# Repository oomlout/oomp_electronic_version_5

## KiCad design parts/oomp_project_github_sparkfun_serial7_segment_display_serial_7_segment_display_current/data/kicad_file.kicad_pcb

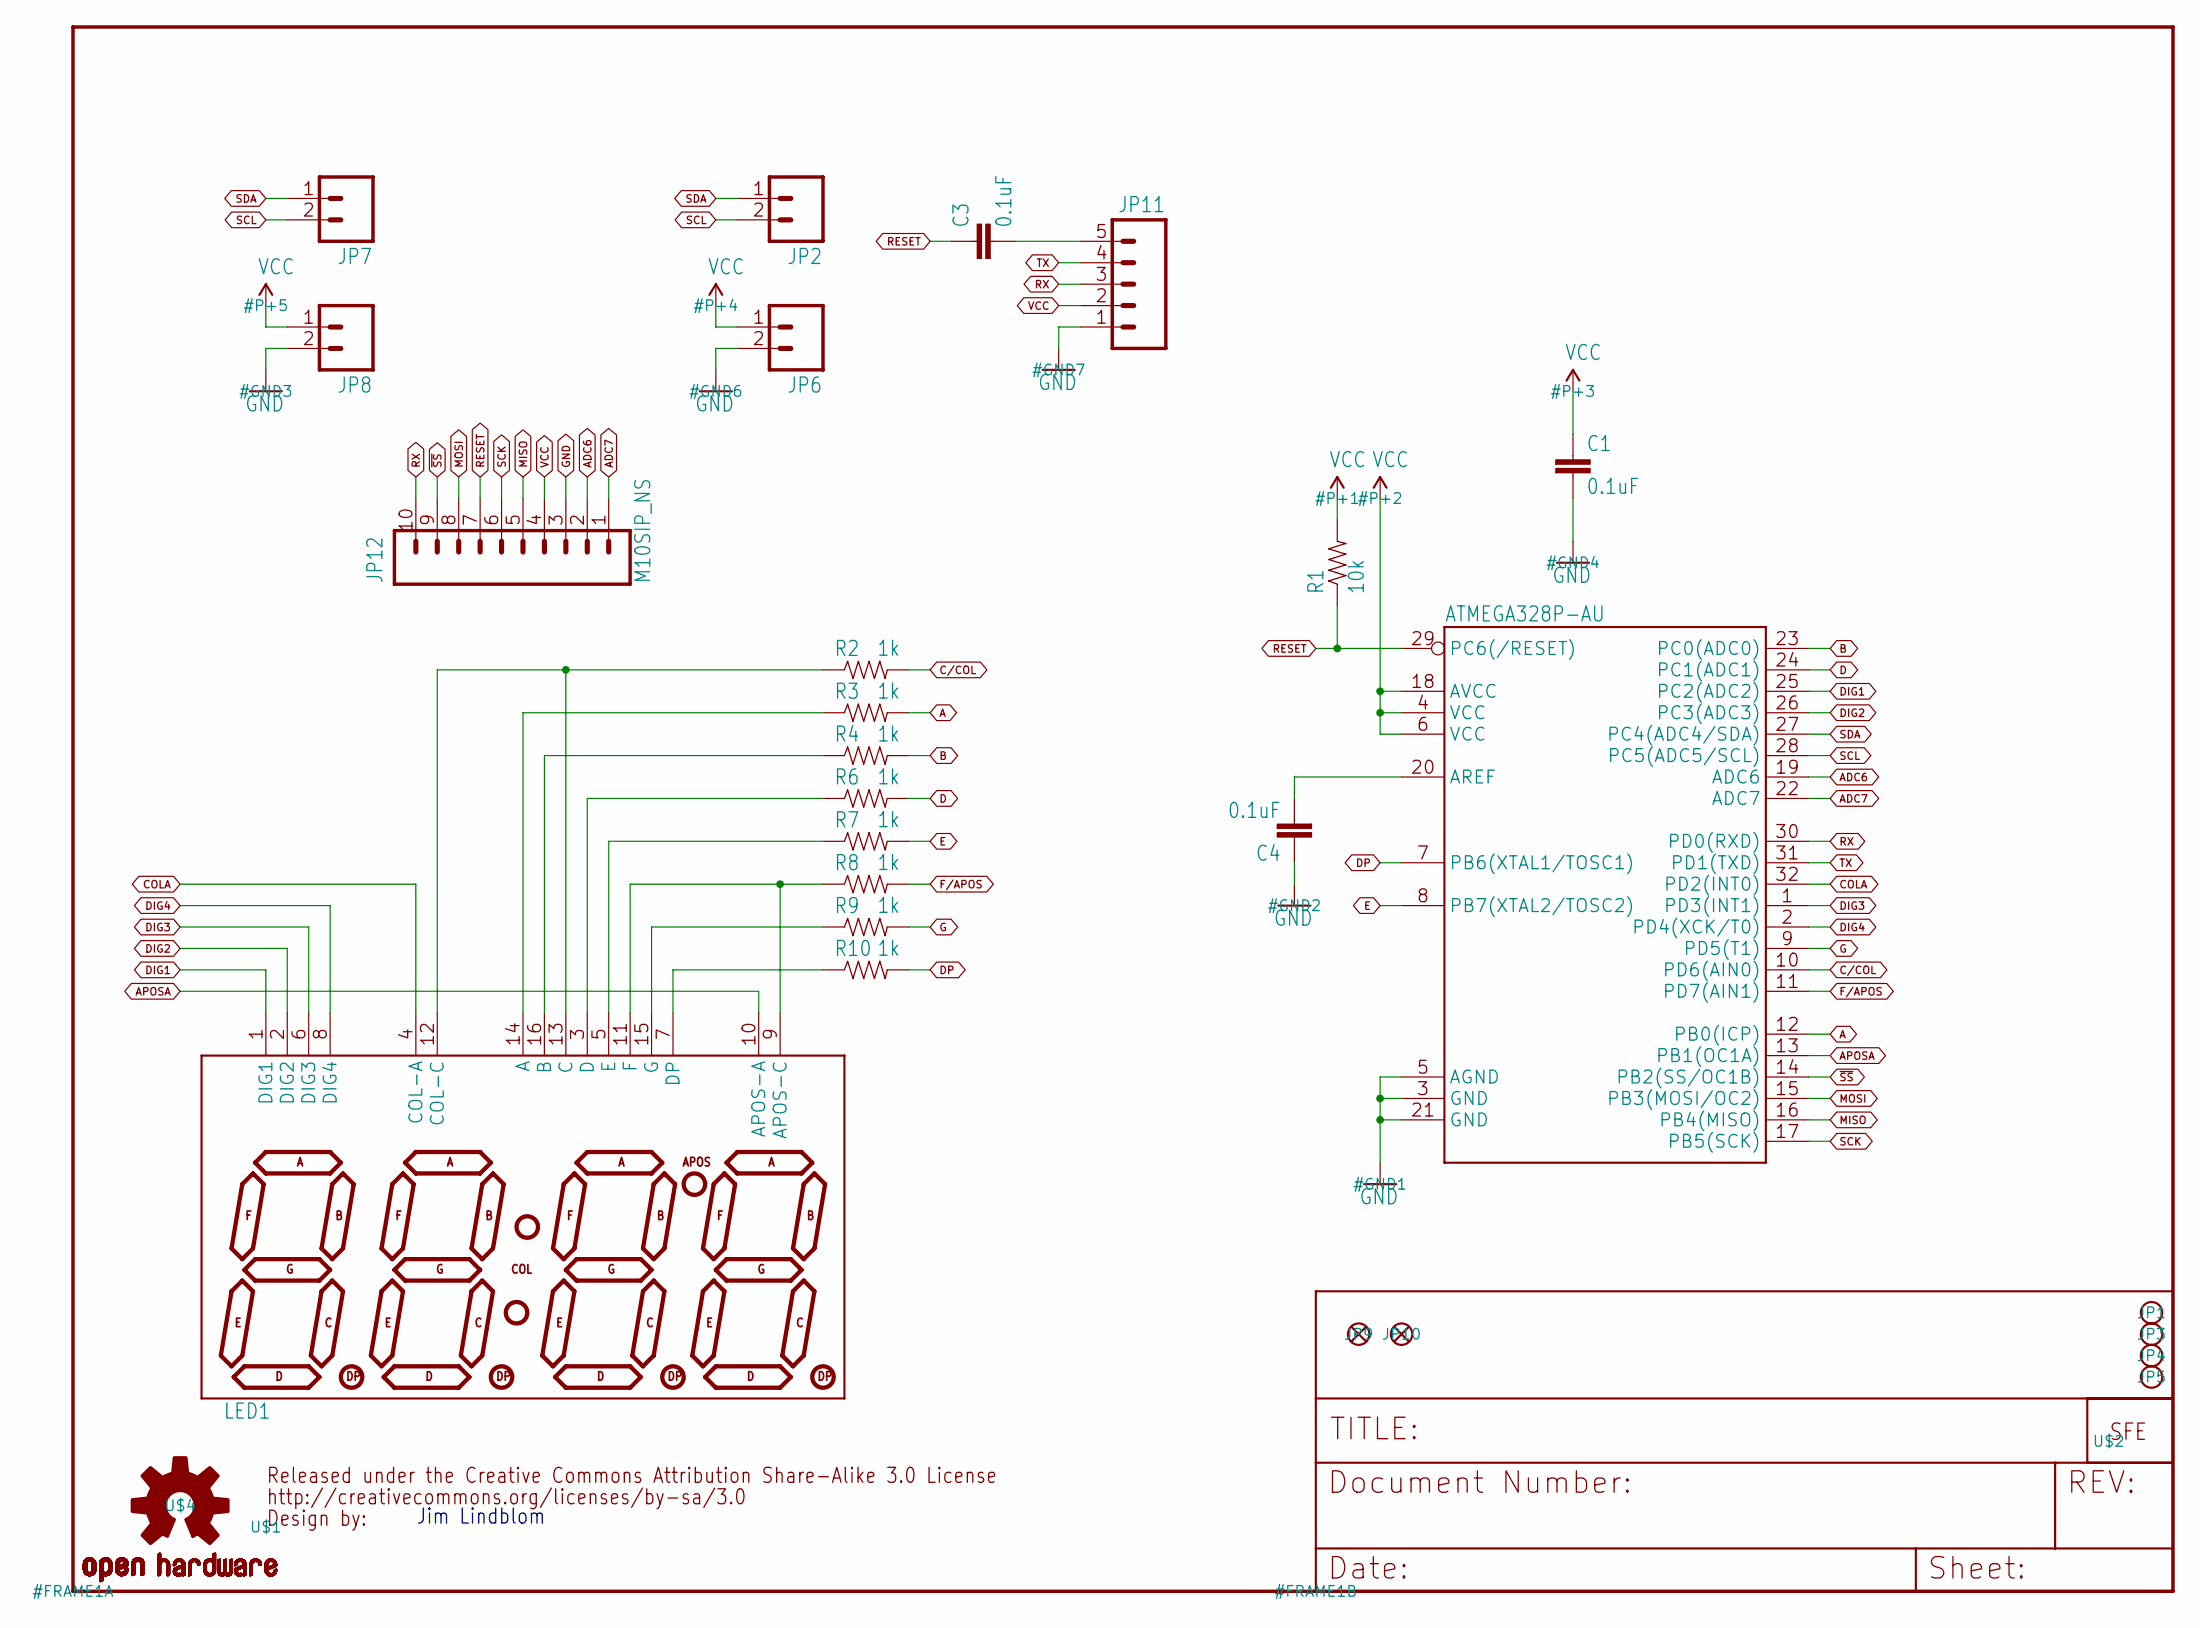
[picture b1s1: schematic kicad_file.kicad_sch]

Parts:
ATMEGA328P-AU0: ATMEGA328P-AU; TQFP32-08
C1, C3, C4: 0.1uF; 0402-CAP
JP1, JP3, JP4, JP5: STAND-OFF
JP2, JP6, JP7, JP8: M021X02_NO_SILK; 1X02_NO_SILK
JP9, JP10: FIDUCIALUFIDUCIAL; MICRO-FIDUCIAL
JP11: M05PTH-NS; 1X05_NO_SILK
JP12: M10SIP_NS; 1X10_NO_SILK
LED1: 7-SEGMENT-4DIGIT-YOUNGSUN
R1: 10k; 0402-RES
R2, R3, R4, R6, R7, R8, R9, R10: 1k; 0402-RES
U$1: CREATIVE_COMMONS
U$2: LOGO-SFESK; SFE-LOGO-FLAME
U$4: OSHW-LOGOS; OSHW-LOGO-S

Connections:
A: ATMEGA328P-AU0.12 (PB0(ICP)), R3.2
ADC6: ATMEGA328P-AU0.19 (ADC6), JP12.2
ADC7: ATMEGA328P-AU0.22 (ADC7), JP12.1
APOSA: ATMEGA328P-AU0.13 (PB1(OC1A)), LED1.10 (APOS-A)
B: ATMEGA328P-AU0.23 (PC0(ADC0)), R4.2
C/COL: ATMEGA328P-AU0.10 (PD6(AIN0)), R2.2
COLA: ATMEGA328P-AU0.32 (PD2(INT0)), LED1.4 (COL-A)
D: ATMEGA328P-AU0.24 (PC1(ADC1)), R6.2
DIG1: ATMEGA328P-AU0.25 (PC2(ADC2)), LED1.1 (DIG1)
DIG2: ATMEGA328P-AU0.26 (PC3(ADC3)), LED1.2 (DIG2)
DIG3: ATMEGA328P-AU0.1 (PD3(INT1)), LED1.6 (DIG3)
DIG4: ATMEGA328P-AU0.2 (PD4(XCK/T0)), LED1.8 (DIG4)
DP: ATMEGA328P-AU0.7 (PB6(XTAL1/TOSC1)), R10.2
E: ATMEGA328P-AU0.8 (PB7(XTAL2/TOSC2)), R7.2
F/APOS: ATMEGA328P-AU0.11 (PD7(AIN1)), R8.2
G: ATMEGA328P-AU0.9 (PD5(T1)), R9.2
GND: ATMEGA328P-AU0.3 (GND), ATMEGA328P-AU0.5 (AGND), ATMEGA328P-AU0.21 (GND), C1.2, C4.1, JP6.2, JP8.2, JP11.1, JP12.3
MISO: ATMEGA328P-AU0.16 (PB4(MISO)), JP12.5
MOSI: ATMEGA328P-AU0.15 (PB3(MOSI/OC2)), JP12.8
unnamed: ATMEGA328P-AU0.20 (AREF), C4.2
unnamed: LED1.7 (DP), R10.1
unnamed: LED1.15 (G), R9.1
unnamed: LED1.9 (APOS-C), LED1.11 (F), R8.1
unnamed: LED1.5 (E), R7.1
unnamed: LED1.3 (D), R6.1
unnamed: LED1.16 (B), R4.1
unnamed: LED1.14 (A), R3.1
unnamed: LED1.12 (COL-C), LED1.13 (C), R2.1
unnamed: C3.2, JP11.5
RESET: ATMEGA328P-AU0.29 (PC6(/RESET)), C3.1, JP12.7, R1.1
RX: ATMEGA328P-AU0.30 (PD0(RXD)), JP11.3, JP12.10
SCK: ATMEGA328P-AU0.17 (PB5(SCK)), JP12.6
SCL: ATMEGA328P-AU0.28 (PC5(ADC5/SCL)), JP2.2, JP7.2
SDA: ATMEGA328P-AU0.27 (PC4(ADC4/SDA)), JP2.1, JP7.1
TX: ATMEGA328P-AU0.31 (PD1(TXD)), JP11.4
VCC: ATMEGA328P-AU0.4 (VCC), ATMEGA328P-AU0.6 (VCC), ATMEGA328P-AU0.18 (AVCC), C1.1, JP6.1, JP8.1, JP11.2, JP12.4, R1.2
~SS: ATMEGA328P-AU0.14 (PB2(SS/OC1B)), JP12.9

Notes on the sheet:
Jim Lindblom

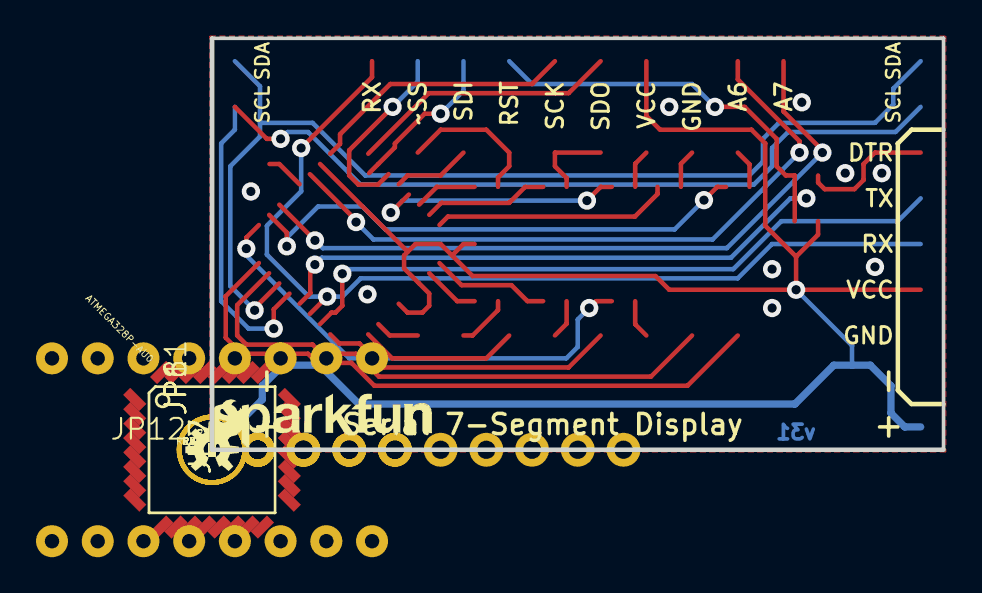
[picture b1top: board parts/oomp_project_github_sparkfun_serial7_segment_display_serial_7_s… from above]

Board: 2 copper layers, 40.6 x 22.9 mm, 30 parts (1 on the bottom side), 37 nets.

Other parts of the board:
U$3: LOGO-SFENW2; SFE-NEW-WEB

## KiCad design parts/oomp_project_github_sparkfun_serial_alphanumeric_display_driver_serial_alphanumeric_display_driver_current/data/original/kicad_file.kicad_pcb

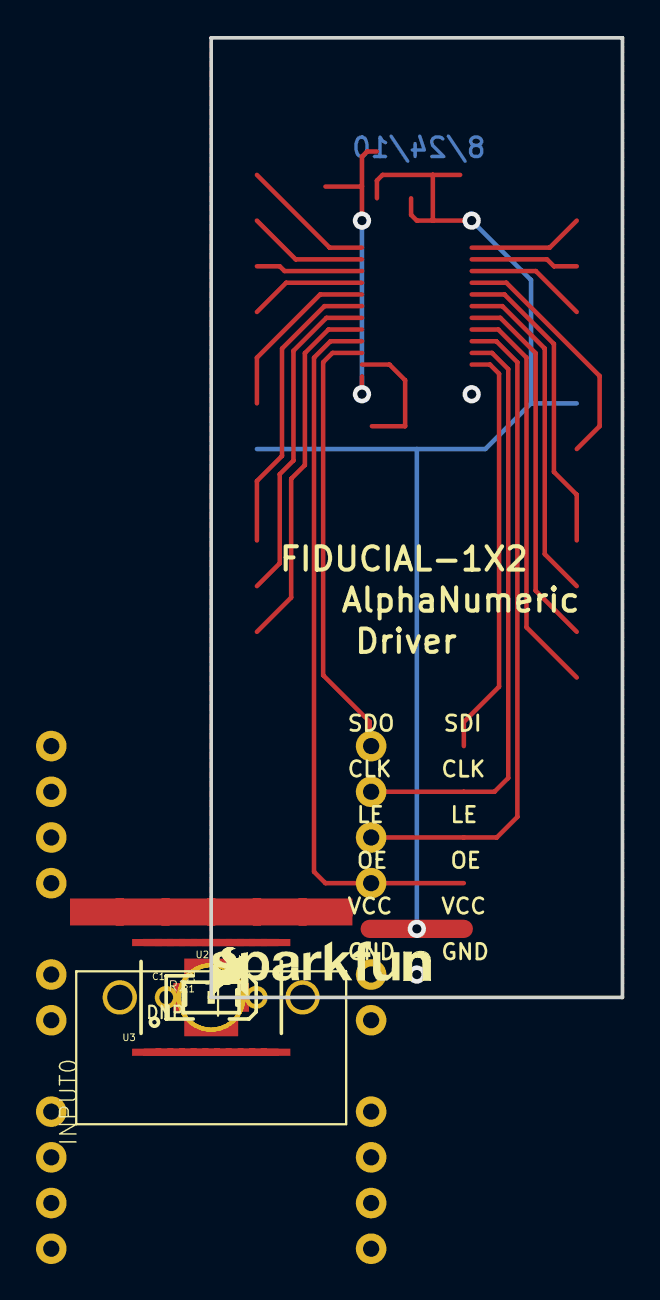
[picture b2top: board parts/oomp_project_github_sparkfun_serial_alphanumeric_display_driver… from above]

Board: 2 copper layers, 22.9 x 53.3 mm, 17 parts (1 on the bottom side), 25 nets.

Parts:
C1: 10uF; EIA3216
C2: 0.1uF; 0402-CAP
INPUT0: 1X06-SMD-FEMALE-V2
JP1, JP5: LOGO-SFESK; SFE-LOGO-FLAME
JP2, JP3: STAND-OFF
JP4: LOGO-SFENW2; SFE-NEW-WEB
JP6, JP7: FIDUCIAL1X2; CREATIVE_COMMONS_2
OUTPUT0: 1X06-SMD
R1: 4.7k; 0402-RES
R2: DNP; 1_6W-RES
U1: DNP; ALPHANUMERIC
U2: V_REG_LDOSMD; SOT23-5
U3: A6282-LP; TSSOP-24
U$1: CREATIVE_COMMONS

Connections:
3.3V: C2.1, U2.5, U3.24
A1: U1.2, U3.12
A2: U1.22, U3.15
B: U1.21, U3.16
C: U1.16, U3.18
CLK: INPUT0.2, OUTPUT0.2, U3.3
D1: U1.10, U3.7
D2: U1.14, U3.20
E: U1.9, U3.8
F: U1.4, U3.10
G1: U1.7, U3.9
G2: U1.19, U3.17
GND: C1.C, C2.2, INPUT0.6, OUTPUT0.6, R1.1, R2.1, U2.2, U3.1, U3.EP
H: U1.3, U3.11
J: U1.24, U3.13
K: U1.23, U3.14
L: U1.15, U3.19
LE: INPUT0.3, OUTPUT0.3, U3.4
M: U1.12, U3.5
N: U1.11, U3.6
OE: INPUT0.4, OUTPUT0.4, U3.21
REXT: R1.2, R2.2, U3.23
SDI: INPUT0.1, U3.2
SDO: OUTPUT0.1, U3.22
VCC: C1.A, INPUT0.5, OUTPUT0.5, U1.6, U1.18, U2.1, U2.3

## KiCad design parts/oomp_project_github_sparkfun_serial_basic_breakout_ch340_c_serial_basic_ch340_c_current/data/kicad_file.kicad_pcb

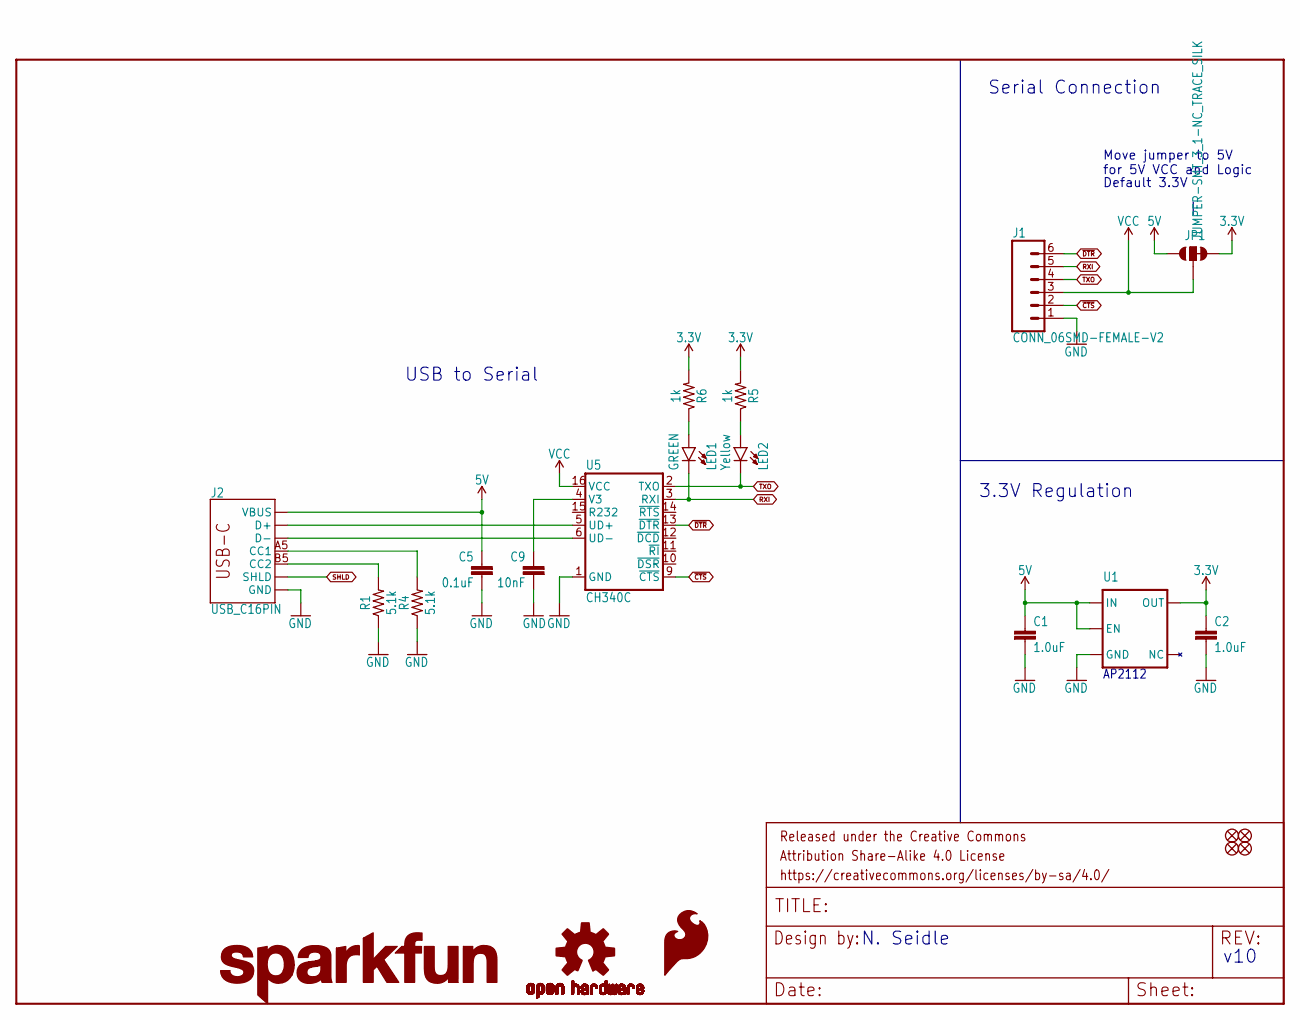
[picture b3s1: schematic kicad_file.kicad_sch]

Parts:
C1, C2: 1.0uF; 0603
C5: 0.1uF; 0603
C9: 10nF; 0603
FRAME1: FRAME-LETTER; CREATIVE_COMMONS
J1: CONN_06SMD-FEMALE-V2; 1X06-SMD-FEMALE
J2: USB_C16PIN; USB-C-16P
JP1: JUMPER-SMT_3_1-NC_TRACE_SILK; SMT-JUMPER_3_1-NC_TRACE_SILK
JP3, JP4, JP5, JP6: FIDUCIAL1X2; FIDUCIAL-1X2
LED1: GREEN; LED-0603
LED2: Yellow; LED-0603
LOGO1: OSHW-LOGOS; OSHW-LOGO-S
LOGO2: SFE_LOGO_FLAME.1_INCH; SFE_LOGO_FLAME_.1
LOGO3: SFE_LOGO_NAME.1_INCH; SFE_LOGO_NAME_.1
R1, R4: 5.1k; 0603
R5, R6: 1k; 0603
U1: 3.3V; SOT23-5
U5: CH340C; SO016

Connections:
3.3V: C2.1, JP1.3, R5.2, R6.2, U1.5 (OUT)
5V: C1.1, C5.1, J2.VBUS1 (VBUS), J2.VBUS2 (VBUS), JP1.1, U1.1 (IN), U1.3 (EN)
CC1: J2.A5 (CC1), R4.2
CC2: J2.B5 (CC2), R1.2
D+: J2.A6 (D+), J2.B6 (D+), U5.5 (UD+)
D-: J2.A7 (D-), J2.B7 (D-), U5.6 (UD-)
GND: C1.2, C2.2, C5.2, C9.2, J1.1, J2.GND, J2.GND2 (GND), R1.1, R4.1, U1.2 (GND), U5.1 (GND)
unnamed: C9.1, U5.4 (V3)
unnamed: LED1.A, R6.1
unnamed: LED2.A, R5.1
RXI: J1.5, LED1.C, U5.3 (RXI)
SHLD: J2.SHLD1 (SHLD), J2.SHLD2 (SHLD), J2.SHLD3 (SHLD), J2.SHLD4 (SHLD), J2.SHLD5 (SHLD), J2.SHLD6 (SHLD), J2.SHLD7 (SHLD), J2.SHLD8 (SHLD)
TXO: J1.4, LED2.C, U5.2 (TXO)
VCC: J1.3, JP1.2, U5.16 (VCC)
~CTS: J1.2, U5.9 (~CTS)
~DTR: J1.6, U5.13 (~DTR)

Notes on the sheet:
3.3V Regulation
v10
Default 3.3V
AP2112
USB to Serial
Serial Connection
N. Seidle
Move jumper to 5V for 5V VCC and Logic

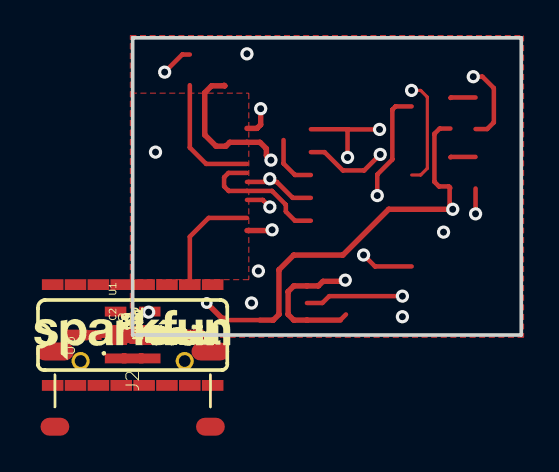
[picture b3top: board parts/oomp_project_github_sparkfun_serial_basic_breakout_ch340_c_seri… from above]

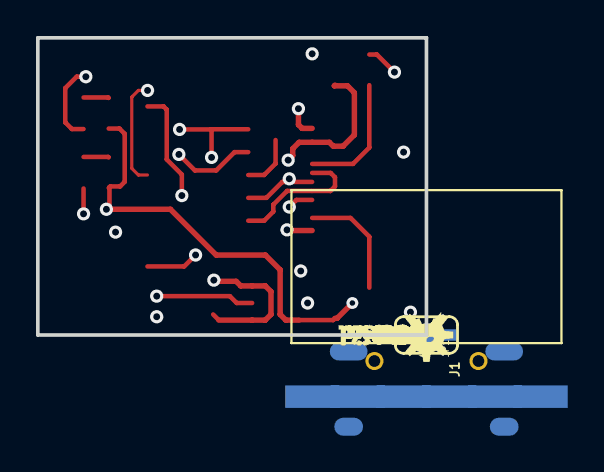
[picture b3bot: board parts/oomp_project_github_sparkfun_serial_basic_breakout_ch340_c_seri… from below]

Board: 4 copper layers, 21.6 x 16.5 mm, 43 parts (16 on the bottom side), 16 nets.

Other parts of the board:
U$1, U$14: CTS1
U$2: 3#3V8
U$3: 5V9
U$4, U$9: SERIAL0
U$5, U$12: TXO0
U$6, U$13: VCC2
U$7, U$11: BASIC1
U$8, U$18: DTR0
U$10, U$21: RXI1
U$15, U$19: GND5
U$17: BLK6
U$20: GRN7

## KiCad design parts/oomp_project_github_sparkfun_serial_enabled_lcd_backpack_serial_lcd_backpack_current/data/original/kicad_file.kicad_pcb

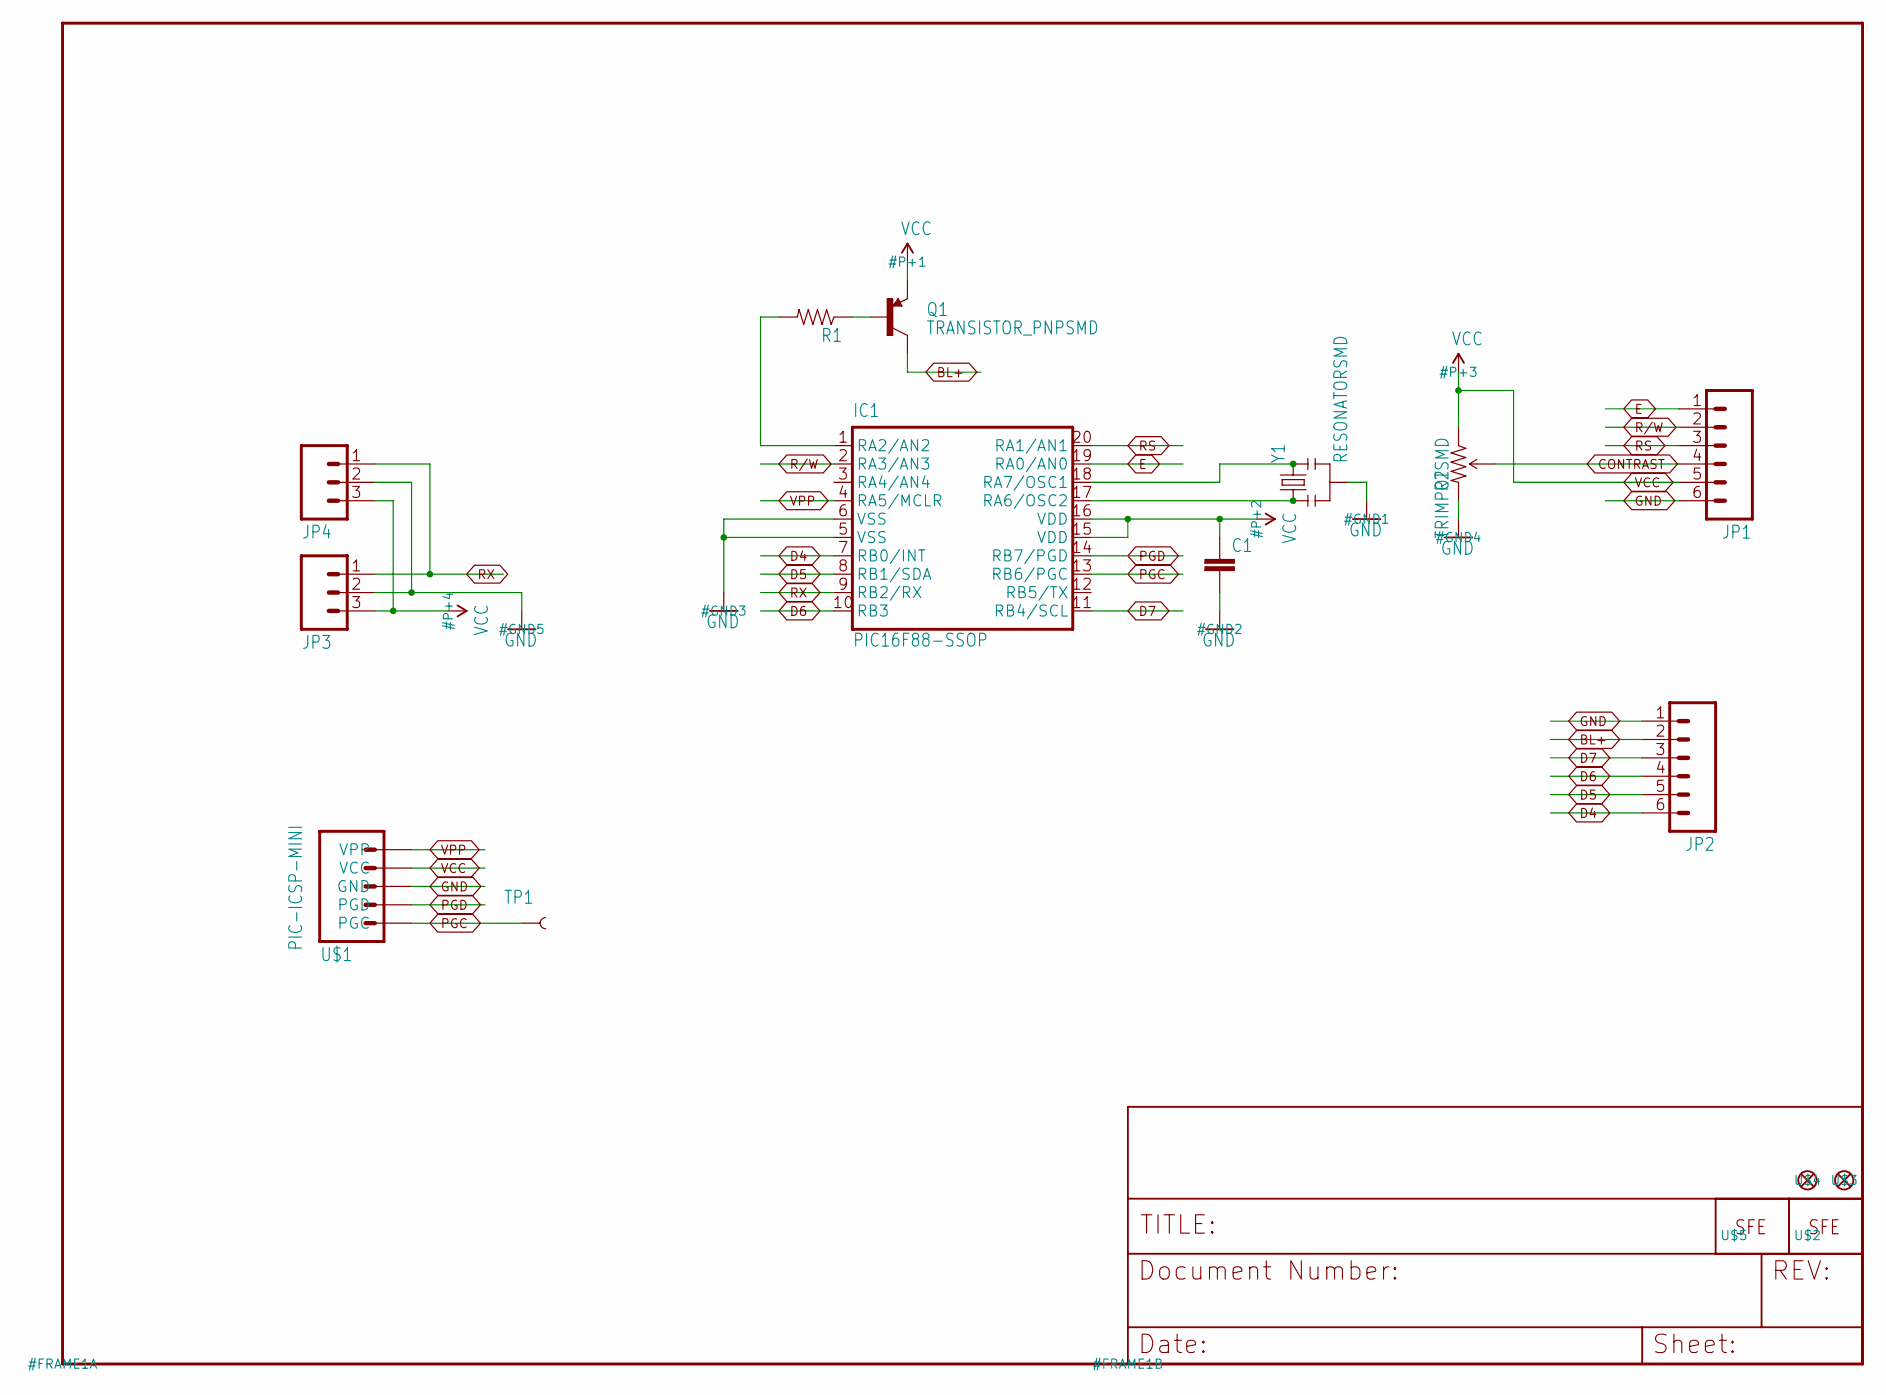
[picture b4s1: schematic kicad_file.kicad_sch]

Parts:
C1: CAP0402-CAP; 0402-CAP
IC1: PIC16F88-SSOP; SSOP20
JP1, JP2: M06LOCK; 1X06_LOCK
JP3: M03PTH; 1X03
JP4: M03SCREW_LOCK; SCREWTERMINAL-3.5MM-3_LOCK.007S
Q1: TRANSISTOR_PNPSMD; SOT23-3
R1: RESISTOR0402-RES; 0402-RES
R2: TRIMPOTSMD; TRIMPOT-3MM
TP1: TEST-POINT3X5; PAD.03X.05
U$1: PIC-ICSP-MINI
U$2: LOGO-FLAME-LARGE
U$3, U$4: FIDUCIAL1X2; FIDUCIAL-1X2
U$5: LOGO-SFENEW; SFE-NEW-WEBLOGO
Y1: RESONATORSMD; RESONATOR-SMD

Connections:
BL+: JP2.2, Q1.3 (C)
CONTRAST: JP1.4, R2.2 (WIPER)
D4: IC1.7 (RB0/INT), JP2.6
D5: IC1.8 (RB1/SDA), JP2.5
D6: IC1.10 (RB3), JP2.4
D7: IC1.11 (RB4/SCL), JP2.3
E: IC1.19 (RA0/AN0), JP1.1
GND: C1.2, IC1.5 (VSS), IC1.6 (VSS), JP1.6, JP2.1, JP3.2, JP4.2, R2.3 (CW), U$1.3 (GND), Y1.2
unnamed: IC1.18 (RA7/OSC1), Y1.3
unnamed: IC1.17 (RA6/OSC2), Y1.1
unnamed: IC1.1 (RA2/AN2), R1.2
unnamed: Q1.1 (B), R1.1
PGC: IC1.13 (RB6/PGC), TP1.P$1, U$1.5 (PGC)
PGD: IC1.14 (RB7/PGD), U$1.4 (PGD)
R/W: IC1.2 (RA3/AN3), JP1.2
RS: IC1.20 (RA1/AN1), JP1.3
RX: IC1.9 (RB2/RX), JP3.1, JP4.1
VCC: C1.1, IC1.15 (VDD), IC1.16 (VDD), JP1.5, JP3.3, JP4.3, Q1.2 (E), R2.1 (CCW), U$1.2 (VCC)
VPP: IC1.4 (RA5/MCLR), U$1.1 (VPP)

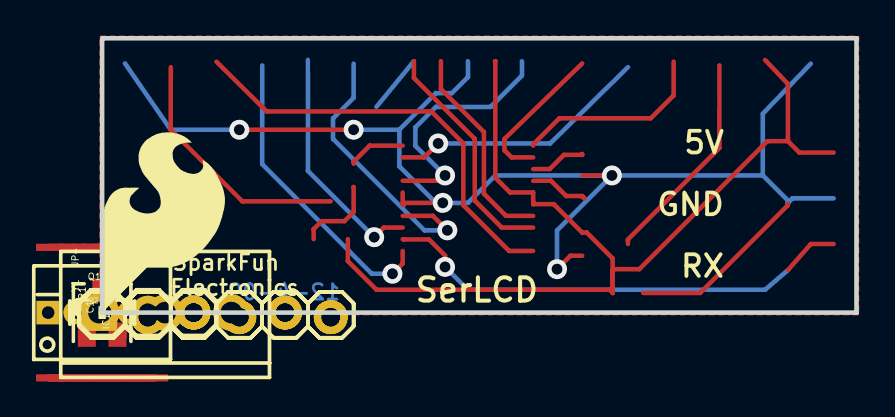
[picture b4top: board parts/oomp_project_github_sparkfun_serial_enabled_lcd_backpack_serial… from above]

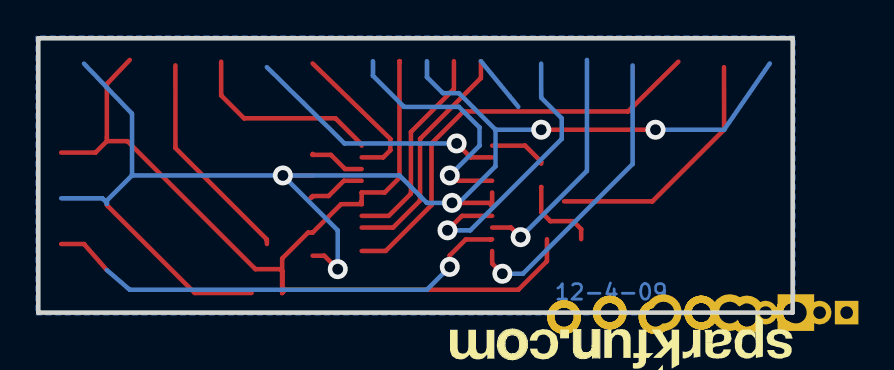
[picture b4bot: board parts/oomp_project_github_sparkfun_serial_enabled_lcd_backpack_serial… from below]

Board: 2 copper layers, 41.9 x 15.2 mm, 16 parts (2 on the bottom side), 19 nets.

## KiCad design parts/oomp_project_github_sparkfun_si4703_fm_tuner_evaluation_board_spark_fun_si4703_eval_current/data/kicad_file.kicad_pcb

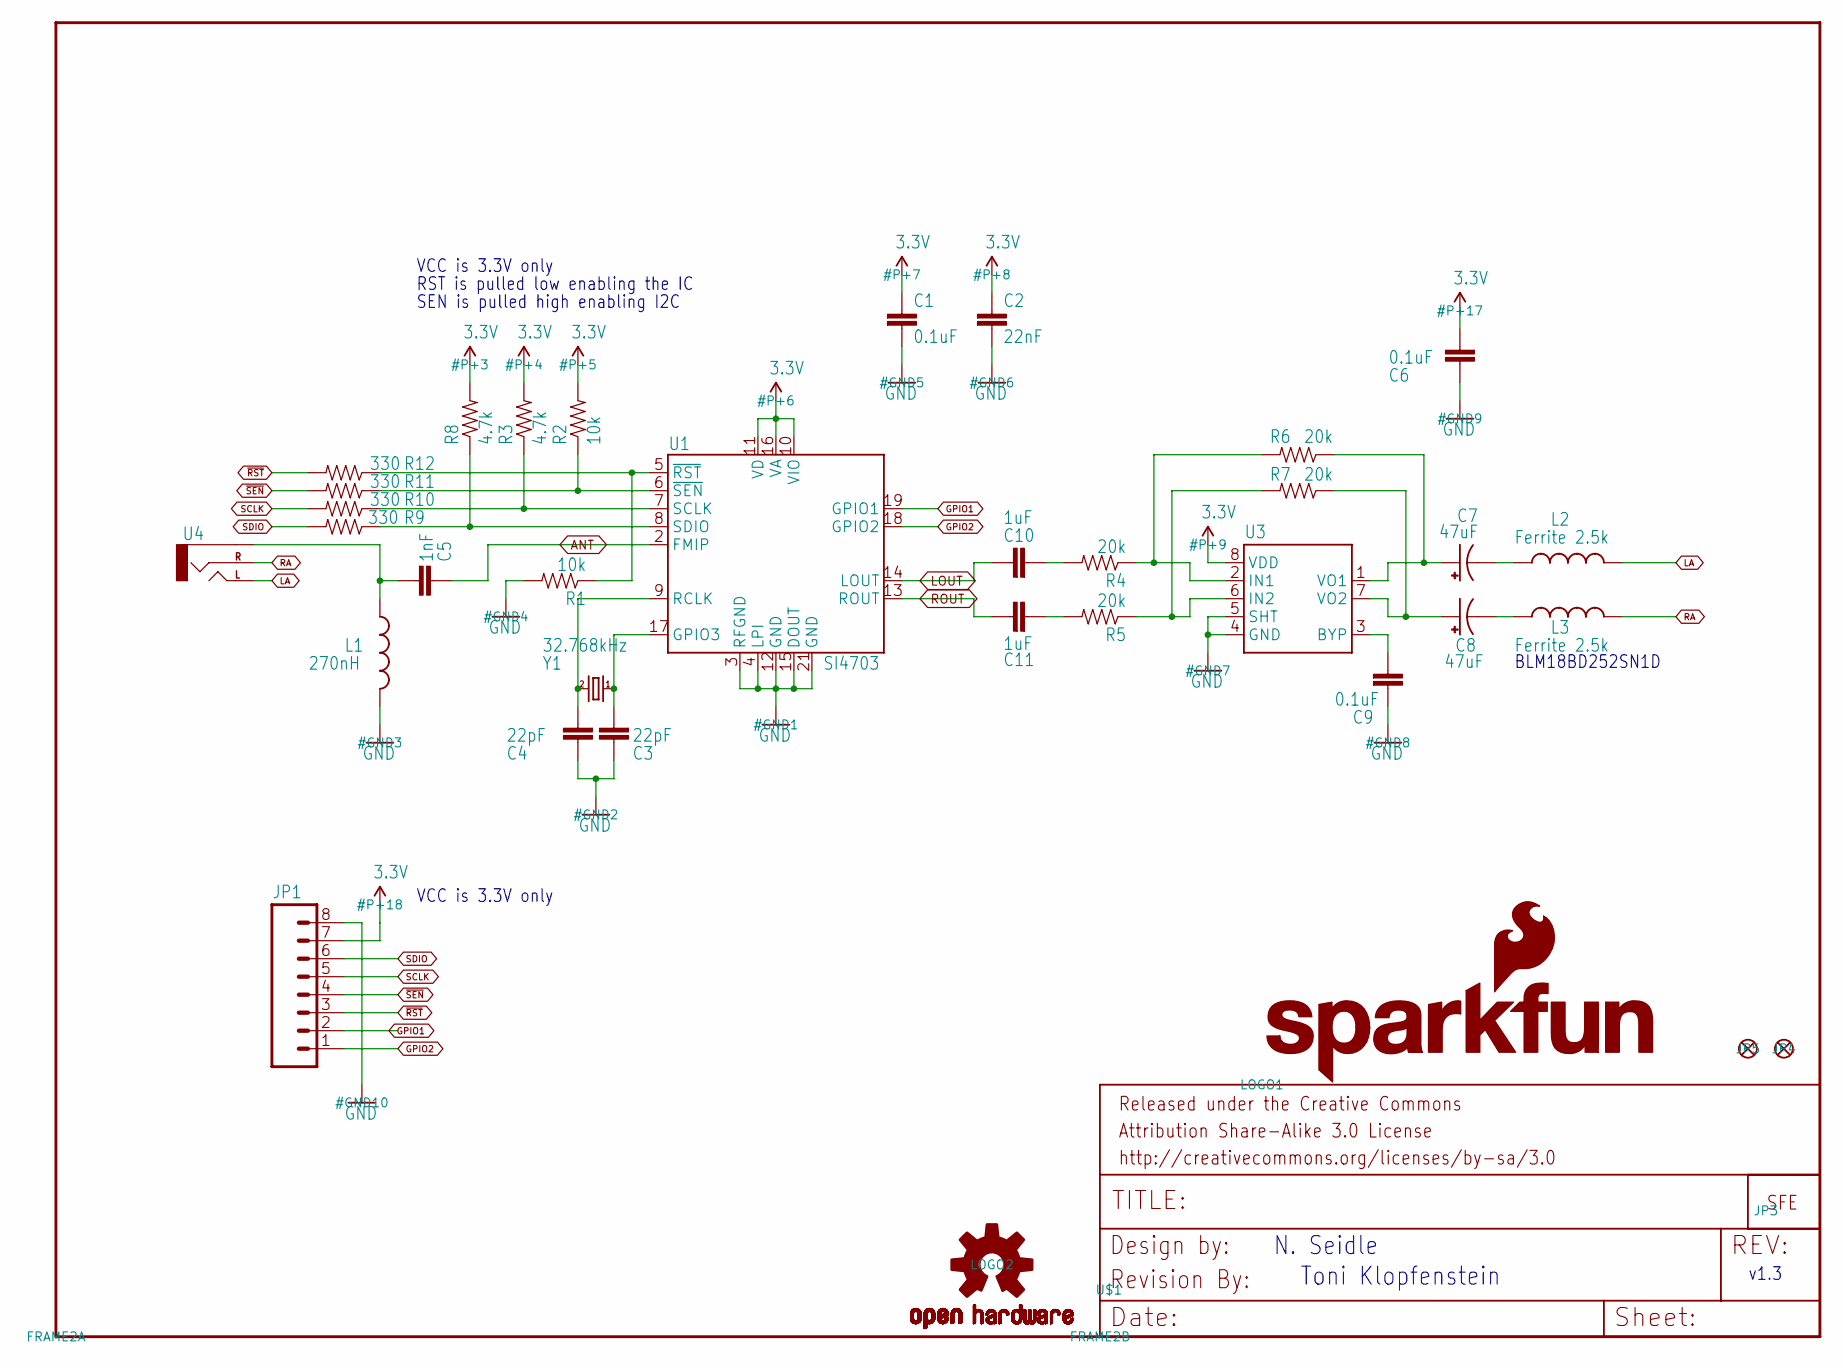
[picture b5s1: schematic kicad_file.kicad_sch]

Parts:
C1, C6, C9: 0.1uF; 0603-CAP
C2: 22nF; 0603-CAP
C3, C4: 22pF; 0603-CAP
C5: 1nF; 0603-CAP
C7, C8: 47uF; EIA3528
C10, C11: 1uF; 0603-CAP
FRAME2: FRAME-LETTER; CREATIVE_COMMONS
JP1: M08; 1X08
JP3: LOGO-SFESK; SFE-LOGO-FLAME
JP4, JP5: FIDUCIAL1X2; FIDUCIAL-1X2
L1: 270nH; 0603
L2, L3: Ferrite 2.5k; 0603
LOGO1: SFE_LOGO_NAME_FLAME.1_INCH; SFE_LOGO_NAME_FLAME_.1
LOGO2: OSHW-LOGOS; OSHW-LOGO-S
R1, R2: 10k; 0603-RES
R3, R8: 4.7k; 0603
R4, R5, R6, R7: 20k; 0603-RES
R9, R10, R11, R12: 330; 0603-RES
U1: SI4703; SI470X
U3: TPA6111; SO08-TIGHT
U4: AUDIO-JACKSMD2; AUDIO-JACK-3.5MM-SMD
U$1: REVISION
Y1: 32.768kHz; CRYSTAL-32KHZ-SMD

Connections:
3.3V: C1.1, C2.1, C6.2, JP1.7, R2.2, R3.2, R8.2, U1.10 (VIO), U1.11 (VD), U1.16 (VA), U3.8 (VDD)
ANT: C5.1, U1.2 (FMIP)
GND: C1.2, C2.2, C3.1, C4.1, C6.1, C9.2, JP1.8, L1.2, R1.2, U1.3 (RFGND), U1.4 (LPI), U1.12 (GND), U1.15 (DOUT), U1.21 (GND), U3.4 (GND), U3.5 (SHT)
GPIO1: JP1.2, U1.19 (GPIO1)
GPIO2: JP1.1, U1.18 (GPIO2)
LA: L2.2, U4.TIP (LEFT)
LOUT: C10.1, U1.14 (LOUT)
unnamed: C4.2, U1.9 (RCLK), Y1.X2 (2)
unnamed: C3.2, U1.17 (GPIO3), Y1.X1 (1)
unnamed: C5.2, L1.1, U4.SLEEVE
unnamed: C7.C (-), L2.1
unnamed: C7.A (+), R6.1, U3.1 (VO1)
unnamed: C8.A (+), R7.1, U3.7 (VO2)
unnamed: C8.C (-), L3.1
unnamed: C9.1, U3.3 (BYP)
unnamed: R4.1, R6.2, U3.2 (IN1)
unnamed: R5.1, R7.2, U3.6 (IN2)
unnamed: C10.2, R4.2
unnamed: C11.2, R5.2
RA: L3.2, U4.RING (RIGHT)
ROUT: C11.1, U1.13 (ROUT)
SCLK: JP1.5, R10.2
SCLK-L: R3.1, R10.1, U1.7 (SCLK)
SDIO: JP1.6, R9.2
SDIO-L: R8.1, R9.1, U1.8 (SDIO)
~RST-L: R1.1, R12.1, U1.5 (~RST)
~RST: JP1.3, R12.2
~SEN-L: R2.1, R11.1, U1.6 (~SEN)
~SEN: JP1.4, R11.2

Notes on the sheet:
VCC is 3.3V only~{}
N. Seidle
Toni Klopfenstein
SEN is pulled high enabling I2C
v1.3
BLM18BD252SN1D
RST is pulled low enabling the IC

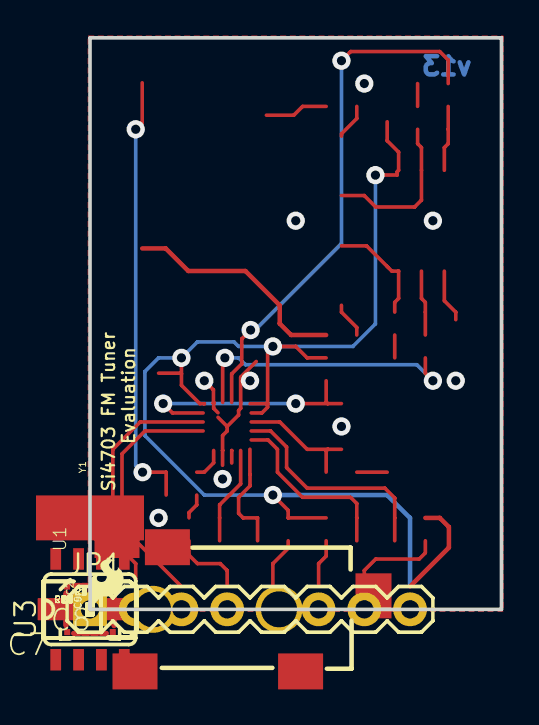
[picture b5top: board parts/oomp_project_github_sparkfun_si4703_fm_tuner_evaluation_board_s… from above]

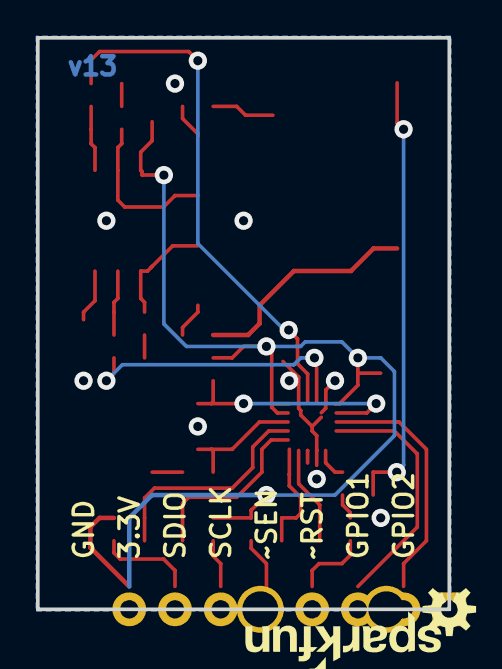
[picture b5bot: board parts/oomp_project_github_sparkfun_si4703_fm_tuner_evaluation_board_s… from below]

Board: 2 copper layers, 22.9 x 31.8 mm, 38 parts (2 on the bottom side), 29 nets.

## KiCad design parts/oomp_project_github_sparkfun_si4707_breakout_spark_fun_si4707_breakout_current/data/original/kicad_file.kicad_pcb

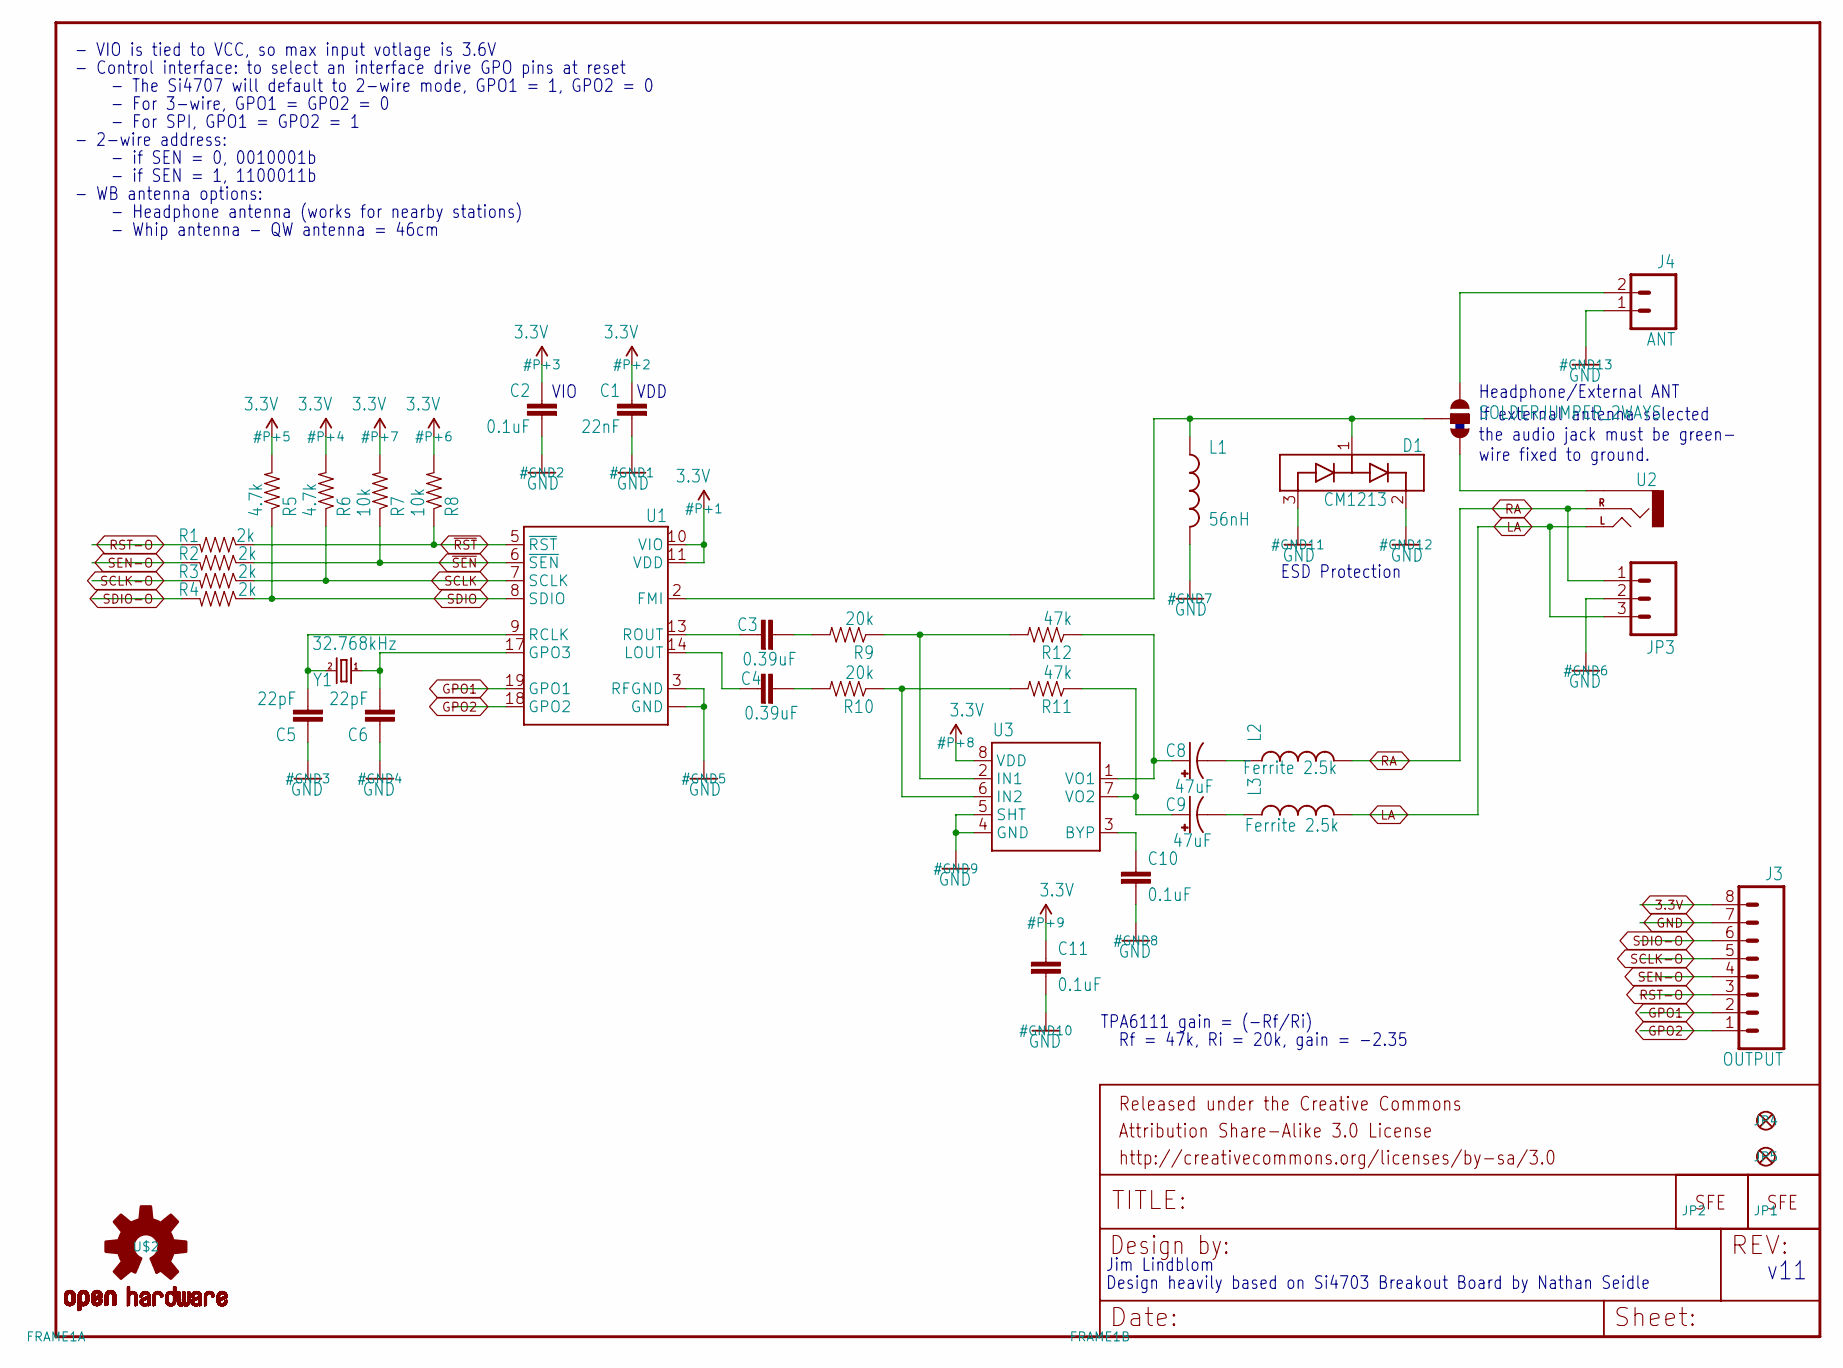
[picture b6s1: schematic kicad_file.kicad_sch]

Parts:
C1: 22nF; 0402-CAP
C2, C10, C11: 0.1uF; 0402-CAP
C3, C4: 0.39uF; 0402-CAP
C5, C6: 22pF; 0402-CAP
C8, C9: 47uF; EIA3528
D1: CM1213; SOT23-3
FRAME1: FRAME-LETTER; CREATIVE_COMMONS
J3: OUTPUT; 1X08
J4: ANT; 1X02
JP1: LOGO-SFENEW; SFE-NEW-WEBLOGO
JP2: LOGO-SFESK; SFE-LOGO-FLAME
JP3: M03PTH; 1X03
JP4, JP5: FIDUCIALUFIDUCIAL; MICRO-FIDUCIAL
L1: 56nH; 0603
L2, L3: Ferrite 2.5k; C0402
R1, R2, R3, R4: 2k; 0402-RES
R5, R6: 4.7k; 0402-RES
R7, R8: 10k; 0402-RES
R9, R10: 20k; 0402-RES
R11, R12: 47k; 0402-RES
SJ2: SOLDERJUMPER_2WAYS; SJ_3
U1: SI4707; SI470X
U2: AUDIO-JACKSMD2; AUDIO-JACK-3.5MM-SMD
U3: TPA6111; SPARKFUN_SO08
U$2: OSHW-LOGOS; OSHW-LOGO-S
Y1: 32.768kHz; CRYSTAL-32KHZ-SMD

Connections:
3.3V: C1.1, C2.1, C11.1, J3.8, R5.2, R6.2, R7.2, R8.2, U1.10 (VIO), U1.11 (VDD), U3.8 (VDD)
GND: C1.2, C2.2, C5.1, C6.1, C10.2, C11.2, D1.2 (VP), D1.3 (VN), J3.7, J4.1, JP3.2, L1.2, U1.3 (RFGND), U1.4 (GND), U1.12 (GND), U1.15 (GND), U1.16 (GND), U1.21 (GND), U3.4 (GND), U3.5 (SHT)
GPO1: J3.2, U1.19 (GPO1)
GPO2: J3.1, U1.18 (GPO2)
J1: D1.1 (CH1), L1.1, SJ2.2, U1.2 (FMI)
LA: JP3.3, L3.2, U2.TIP (LEFT)
LOUT: C4.1, U1.14 (LOUT)
unnamed: C3.2, R9.2
unnamed: C4.2, R10.2
unnamed: C6.2, U1.17 (GPO3), Y1.X1 (1)
unnamed: SJ2.1, U2.SLEEVE
unnamed: J4.2, SJ2.3
unnamed: R9.1, R12.2, U3.2 (IN1)
unnamed: R10.1, R11.2, U3.6 (IN2)
unnamed: C10.1, U3.3 (BYP)
unnamed: C8.C (-), L2.1
unnamed: C9.C (-), L3.1
unnamed: C8.A (+), R12.1, U3.1 (VO1)
unnamed: C9.A (+), R11.1, U3.7 (VO2)
RA: JP3.1, L2.2, U2.RING (RIGHT)
RCLK: C5.2, U1.9 (RCLK), Y1.X2 (2)
ROUT: C3.1, U1.13 (ROUT)
RST-O: J3.3, R1.2
SCLK: R3.1, R6.1, U1.7 (SCLK)
SCLK-O: J3.5, R3.2
SDIO: R4.1, R5.1, U1.8 (SDIO)
SDIO-O: J3.6, R4.2
SEN-O: J3.4, R2.2
~RST: R1.1, R8.1, U1.5 (~RST)
~SEN: R2.1, R7.1, U1.6 (~SEN)

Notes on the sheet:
TPA6111 gain = (-Rf/Ri)
- Control interface: to select an interface drive GPO pins at reset
- Whip antenna - QW antenna =~{} 46cm
VIO
- Headphone antenna (works for nearby stations)
Headphone/External ANT
- VIO is tied to VCC, so max input votlage is 3.6V
- The Si4707 will default to 2-wire mode, GPO1 = 1, GPO2 = 0
Design heavily based on Si4703 Breakout Board by Nathan Seidle
- if SEN = 0, 0010001b
Rf = 47k, Ri = 20k, gain = -2.35
v11
VDD
If external antenna selected the audio jack must be green- wire fixed to ground.
- For SPI, GPO1 = GPO2 = 1
Jim Lindblom
- WB antenna options:
ESD Protection
- if SEN = 1, 1100011b
- 2-wire address:
- For 3-wire, GPO1 = GPO2 = 0

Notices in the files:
parts/oomp_project_github_sparkfun_serial7_segment_display_serial_7_segment_display_current/data/kicad_file.kicad_sch:
Released under the Creative Commons Attribution Share-Alike 3.0 License
http://creativecommons.org/licenses/by-sa/3.0
parts/oomp_project_github_sparkfun_serial_basic_breakout_ch340_c_serial_basic_ch340_c_current/data/kicad_file.kicad_sch:
https://creativecommons.org/licenses/by-sa/4.0
parts and their libraries:
Released under the Creative Commons Attribution Share-Alike 4.0 License
